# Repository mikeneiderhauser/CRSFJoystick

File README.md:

# ELRSJoystick / CRSFJoystick

<https://github.com/mikeneiderhauser/CRSFJoystick>

Named CRSFJoystick as it indicates the wire protocol between the microcontroller (pi pico) and receiver).

Arduino code using the mbed core that runs on a Pi Pico (2040) to emulate a USB HID Joystick

Pirmarily developed to use and ExpressLRS receiver and a HID Joystick for Sim use! It will work with both Tracer and Crossfire as well.

Shout out to CapnBry for the Crsf Library

https://github.com/CapnBry/CRServoF

Shout out to RealRobots.net for the Gamepad Library

https://gitlab.com/realrobots/PicoGamepad/-/tree/master

# Future Plans

- GitHub Builds
- Rework HID USB code
- Add failsafe nopulses / hold

# Demo Video

## Purchase

Originally offered of FPVExchange, but that is no longer an option. Please send me an email for availability, purchase, or to get additional info!

<housefpv@gmail.com>

You can also contact me on discord [HouseFPV](https://discordapp.com/users/HouseFPV#5899)

- Blank carrier boards for Pi Pico, Tiny 2040, and Waveshare RP2040 (old stock)
- Built and flashed units
- [DIY Section](#diy-hardware)

A few boards that I believe are based off of this project:
- HGLRC Dongle (I have samples from HGLRC on the way)
  - [HGLRC Dongle at HGLRC](https://www.hglrc.com/collections/new-arrivals/products/hglrc-c1-remote-control)
  - [HGLRC C1 Radio Kit with dongle at HGLRC](https://www.hglrc.com/collections/new-arrivals/products/hglrc-c1-remote-control)
  - [HGLRC C1 Radio Kit with dongle at RacedayQuads](https://www.racedayquads.com/products/hglrc-c1-transmitter-elrs-2-4ghz-choose-your-version?keyword=hglrc%20c1)
- Squid Stick (I have personally not tested one)
  -  [Squid Stick at Progressiverc.com](https://www.progressiverc.com/products/squid-stick-elrs-2-4ghz-usb-receiver-module)
  -  Squid Stick at RacedayQuads - Link to be posted when available
- YMZFPV Simulator Adapter (have not yet been able to confirm that this is based off of this project)
  - [YMZFPV Sim Adapter at RacedayQuads](https://www.racedayquads.com/products/ymzfpv-wireless-simulator-adapter-for-sbus-pwm-csfr-choose-your-version?keyword=simulator)

## Compatability

This project was designed primarily with ELRS usage in mind, however this code base has also been tested with TBS Crossfire Receivers (915MHZ) (last tested v6.16) and TBS Tracer Receivers (2.4GHz) (last tested v6.17) and both appear to work! Flight was teseted in the Liftoff simulator.

I no longer have TBS Crossfire nor TBS Tracer TX modules or Receivers so future tests will have to be conducted by others.

### ExpressLRS (Waveshare RP2040)

### Crossfire

### Tracer

# Building / Flashing

I recently converted the projet to PlatformIO to aid in building, board management, etc.  PlatformIO has some known quirks with PiPico boards and I'm going to leave some breadcrumbs here for later.

## VSCode with PlatformIO

### Installing VSCode and PlatformIO
<https://platformio.org/install/ide?install=vscode>

### Build for specific board / environment

At the Bottom of VSCode you will see a tool bar.  Look for `Default (CRSFJoystick)`.  Building in this state will build for all boards / environments defined in the `platformio.ini` file.  To target a sepecific board, Click on `Default (CRSFJoystick)` and select an appropriate option (Note, selection pops up at the top of vscode).

Click on the Checkmark on the bottom toolbar to build for the board / environment you selected.

Click on the `->` on the bottom toolbar to upload to the board.  If upload fails to find your board, please see bothe the [alternative upload](#alternative-upload) section as well as the driver section.

## Alternative upload
This is one of the standard advertised methods for uploading firmware to a pipico based microcontroller board.

Press and hold the bootsel button on your board and either plugin/power on the board or if the board is already powered press and release the reset button.

This will put the board in RP2 Boot mode.

A removable device should pop up or become available on your computer.  Drag and drop the `firmware.u2f` file from the `.pio/build/wavesharerp2040zero/` directory into this device on your computer.  Note replpace wavesharerp2040zero with the environment for your board.

## Drivers
Drivers can be hit or miss for the pipico board and platformio.  

You may need to use zadig to get vscode+platforio to be able to upload directly to the board.
<https://github.com/platformio/platform-raspberrypi/issues/2#issuecomment-828586398>

Below are the drivers I have working on my Windows 11 machine.  You may need to modify the driver selection via zadig and or device manager to get it working.

- Standard Running Mode
  - RaspberryPi Pico (Interface 0)
    - Zadig -> HidUsb v10.0.22621.819
    - Device Manager -> Human Interface Devices -> HID-compliant game controller
  - RaspberryPi Pico (Interface 1)
      - Zadig -> usbser v10.0.22621.1778
      - Device Manager -> Ports (COM & LPT) -> USB Serial Device
- RP2 Boot mode
  - RP2 Boot (Interface 0) 
    - Zadig USBSTOR v10.0.022621.1778 
    - Device Manager -> Disk Drives -> RPI RP2 USB Device 
  - RP2 Boot (Interface 1)
    - Zadig WinUSB v6.1.7600.16385
    Device Manager -> Universal Serial Bus Devices -> RP2 Boot

### Device manager clicks to change driver 
Right Click -> Properties -> Update Driver -> Browse my computer for drivers -> Let me pick from a list of available drivers on my computer

# Flashing ELRS Receiver

Depending on the device you are using, your target may be different.  For all of the DIY version's I've made, I used the HappyModel EP2 Rx.  Other vendors may vary.

## Flashing via Betaflight Passthrough
<https://www.expresslrs.org/software/updating/betaflight-passthrough/>

## Flashing via Wifi
If your receiver is wifi enabled you can also flash it via wifi

<https://www.expresslrs.org/software/updating/wifi-updating/>

# Testing
For a quick test of functionality, I typically go to [GamepadTester](https://hardwaretester.com/gamepad).

Once the Radio is bound to the RX, it should show up in GamePadTester.

# Mappings
This was a quick map and is not fully featured.

On link up/down the onboard Pi Pico LED will light indicating connection

*NOTE* Channel 5, 6, 7, and 8 are mapped both to analog axis as well as joystick buttons.

| Channel     | Logical Mapping  | Joystick Mapping |
| ----------- | ---------------- | ---------------- |
| 1           | A                | X                |
| 2           | E                | Y                |
| 3           | T                | Rx               |
| 4           | R                | Ry               |
| 5           | Channel 5 (Full) AND AUX1 (1510-2011) | Z  AND Button 0 |
| 6           | Channel 6 (Full) AND AUX2 (1510-2011) | Rz AND Button 1 |
| 7           | Channel 7 (Full) AND AUX3 (1510-2011) | S0 AND Button 2 |
| 8           | Channel 8 (Full) AND AUX4 (1510-2001) | S1 AND Button 3 |
| 9           | AUX5 (1510-2011) | Button 4         |
| 10          | AUX6 (1510-2011) | Button 5         |
| 11          | AUX7 (1510-2011) | Button 6         |
| 12          | AUX8 (1510-2011) | Button 7         |
| 13          | Not Used         | Not Used         |
| 14          | Not Used         | Not Used         |
| 15          | LQ - Not Used    | Not Used         |
| 16          | RSSI - Not Used  | Not Used         |

*Note additional button mappings can be created in caliration.h*

# Here below is for DIY Builds and may be slightly outdated
# DIY Hardware

In a nutshell, wire the ELRS RX up to a uart on the pipico, 5v, and gnd.

| Raspberry Pico | ELRS/CRSF Receiver |
| -------------- | ------------------ |
| VBUS (PIN 40)  | 5V                 |
| GND  (PIN 38)  | GND
| GP4  (PIN 6)   | RX                 |
| GP5  (PIN 7)   | TX                 |

Other boards are supported, see the [board_defs.h](./include/board_defs.h) file.

| Part  | Link | Approx Cost |
| ----- | ---- | ------------|
| Pi Pico | https://www.pishop.us/product/raspberry-pi-pico/ | $4 (Approx $6 with shipping) |
| Waveshare RP2040 zero | https://www.amazon.com/RP2040-Zero-Development-Microcontroller-Multi-Function-Integration/dp/B09SBCKYSC/ref=sr_1_1_sspa?crid=1NDXW0KFV39DX&keywords=waveshare+rp2040+zero&qid=1697989796&sprefix=waveshare+rp2040+zero%2Caps%2C66&sr=8-1-spons&sp_csd=d2lkZ2V0TmFtZT1zcF9hdGY&psc=1| $10|
| Tiny 2040 (alt part) | https://www.pishop.us/product/tiny-2040/ | $10 (Approx $12 with shipping) |
| ELRS RX (any will do) |  https://www.racedayquads.com/products/happymodel-2-4ghz-ep2-tcxo-rx-express-lrs-receiver?keyword=expresslrs | $18 |

Note, price breaks can be had when purchasing at quantity.

Approx part cost for pico hardware (large footprint, cheaper) - $20-$25

- Pi Pico - $4.00
- ELRS RX - $13.50 
- Carrier Board - $1.00 (approx)
- Shipping / Tax from vendors - varies

# Carrier Boards

## ELRSJoystick

This board has an ELRS RX built in, so you don't need to wire any RX on, just plug in and connect to your ELRS TX, then you are ready to go!

## Tiny Version

> **_NOTE:_** References to level shifters below are no longer needed as the level shifter can be omitted. You will have to bridge the pads on the level shifter for the TX/RX pins or use a newer version of the carrier board.

I personally use the Waveshare RP2040-Zero version for my ELRS Joystick!

Hardware build files are located in hardware/kicad/CRSFJoystick/output/Rev1.0

I used JLCPCB with Black Soldermask and a board thickness of 1.6mm.

Note the different orientation of the ELRS RX's.  The orientation can be flipped.  I installed each RX to ensure the boot pad is exposed should the RX need recovered.

## Waveshare RP2040-Zero

[WaveShare RP2040-Zero Board](https://www.waveshare.com/rp2040-zero.htm)

## Raspberry Pi Pico (Full Version)

## Tiny2040

## SEEED AXIO 2040

Board files now in the hardware folder.  Not built or tested but should work.

[SEEED XAIO RP2040 Board](https://www.seeedstudio.com/XIAO-RP2040-v1-0-p-5026.html)

## CRSFJoystick2.0

Build a smaller pico by yourself.

# General Assembly

- Print the top and bottom enclosure
- Print 2 of the spacers for the Pi2040, Print 4 of the spacers for the Pi Pico version
- Follow the directions in this video https://youtu.be/Zuhfbobgm5A

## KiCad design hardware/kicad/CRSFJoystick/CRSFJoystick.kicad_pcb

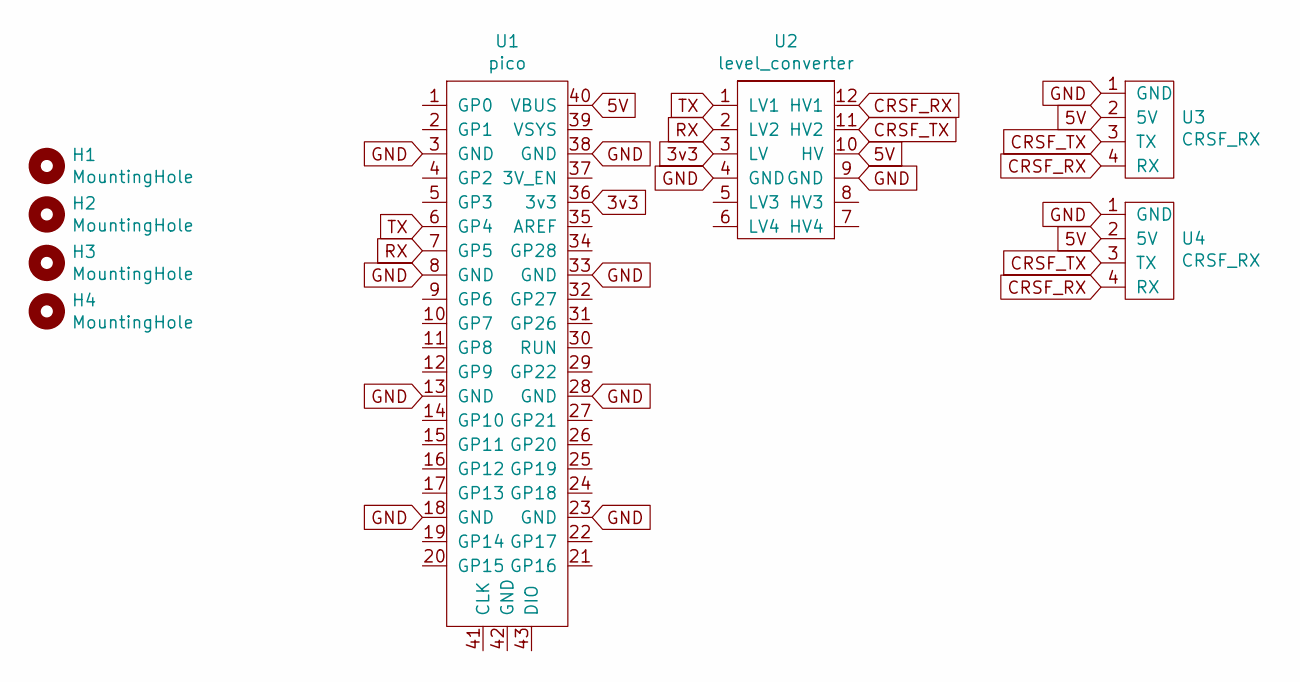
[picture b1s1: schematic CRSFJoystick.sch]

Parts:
H1, H2, H3, H4: MountingHole; MountingHole_2.2mm_M2
U1: pico; pico_no_swd
U2: level_converter
U3, U4: CRSF_RX; ELRS_EP2

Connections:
3v3: U1.36 (3v3), U2.3 (LV)
5V: U1.40 (VBUS), U2.10 (HV), U3.2 (5V), U4.2 (5V)
CRSF_RX: U2.12 (HV1), U3.4 (RX), U4.4 (RX)
CRSF_TX: U2.11 (HV2), U3.3 (TX), U4.3 (TX)
GND: U1.3 (GND), U1.8 (GND), U1.13 (GND), U1.18 (GND), U1.23 (GND), U1.28 (GND), U1.33 (GND), U1.38 (GND), U2.4 (GND), U2.9 (GND), U3.1 (GND), U4.1 (GND)
RX: U1.7 (GP5), U2.2 (LV2)
TX: U1.6 (GP4), U2.1 (LV1)

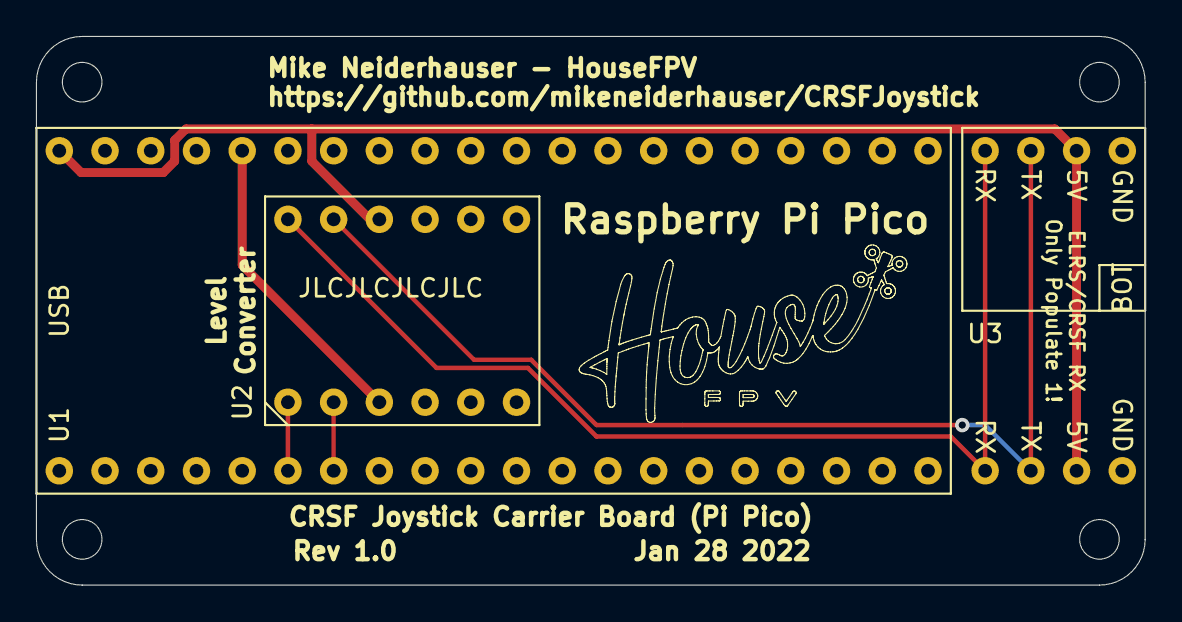
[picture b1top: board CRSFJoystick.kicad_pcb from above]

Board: 2 copper layers, 61.6 x 30.5 mm, 8 parts (1 on the bottom side), 7 nets.

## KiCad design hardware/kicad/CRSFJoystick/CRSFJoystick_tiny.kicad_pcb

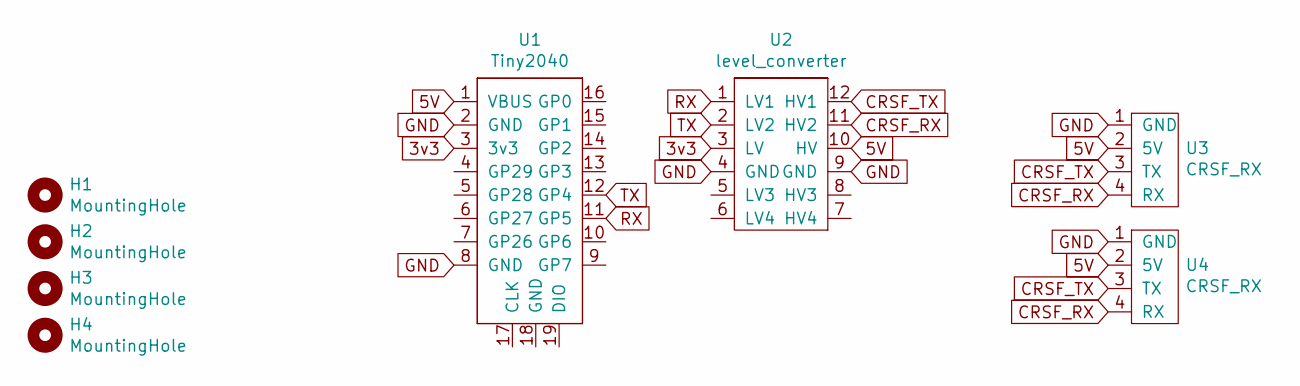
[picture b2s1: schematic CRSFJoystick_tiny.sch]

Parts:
H1, H2, H3, H4: MountingHole; MountingHole_2.2mm_M2
U1: Tiny2040; tiny2040_no_swd
U2: level_converter
U3, U4: CRSF_RX; ELRS_EP2

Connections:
3v3: U1.3 (3v3), U2.3 (LV)
5V: U1.1 (VBUS), U2.10 (HV), U3.2 (5V), U4.2 (5V)
CRSF_RX: U2.11 (HV2), U3.4 (RX), U4.4 (RX)
CRSF_TX: U2.12 (HV1), U3.3 (TX), U4.3 (TX)
GND: U1.2 (GND), U1.8 (GND), U2.4 (GND), U2.9 (GND), U3.1 (GND), U4.1 (GND)
RX: U1.11 (GP5), U2.1 (LV1)
TX: U1.12 (GP4), U2.2 (LV2)

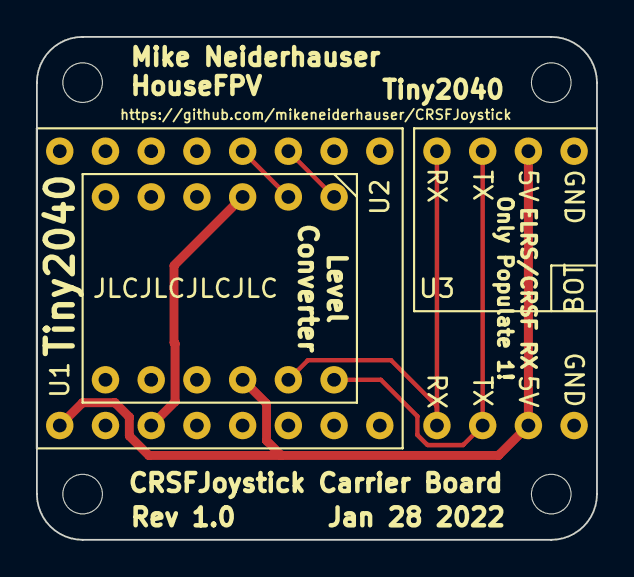
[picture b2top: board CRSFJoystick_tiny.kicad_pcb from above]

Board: 2 copper layers, 31.1 x 27.9 mm, 8 parts (1 on the bottom side), 7 nets.

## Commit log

2022-01-20 Initial checkin
2022-01-20 Add some usage instructions and future plans
2022-01-21 Add ability to map aux ranges to buttons. Multi position support
2022-01-21 Add Demo vid. Configurable buttons
2022-01-29 Add kicad project files and gerber files
2022-01-29 Add proto carrier boards to README
2022-02-25 Add Build Photos
2022-03-03 Update Channel mapping to support first 4 aux channels as full resolution
2022-03-14 add stl files for enclosures
2022-03-14 changes to readme adding prints and level shifter pictures
2022-03-19 Port to Seeed XIAO RP2040
    Added port to Seeed XIAO RP2040 that uses Adafruit TinyUSB.
    Need to install the Seeed XIAO RP2040 board and slect the Adafruit TinyUSB stack to build.
2022-04-02 Add UART define for SEEED XIAO board
2022-04-12 Add LED Libs
2022-04-12 Code changes for board specific LED changes
2022-04-12 Add firmware elf and uf2 for 1.0.1
2022-05-02 Add gerber files for R1.1 that removes level converter
2022-05-02 Added Waveshare RP2040-Zero files
2022-05-08 Add XIAO RP2040 board
2022-05-23 changes to readme adding prints and pictures for Waveshare 2040
2022-06-04 Defaulting to Waveshare board. Removing typo in setup
2022-11-11 Support for Pro Micro.
2022-11-29 New 2.0 version 1. A new usb version hardware. 2. Update all libraries to the latest version.
2022-11-29 added case for CRSFJoystick2.0
2022-11-29 add case for CRSFJoystick2.0
2022-11-29 move gerber file to a new folder
2022-11-29 2.0 version 1. A new usb version hardware. 2. Update all libraries to the latest version.
2022-11-29 add bom file
2022-11-30 fixed a bom error
2022-12-28 v2.2 version
2022-12-28 slightly change
2023-02-02 v2.4
2023-02-02 v2.3
2023-02-10 small modifications
2023-03-13 1.button mapping is now the same as EdgeTX default 2.led blinks when connection is down(same as ELRS)
2023-03-13 changed readme
2023-03-21 LED blinks for 60 sec when connection is down.
2023-03-22 Implement 60 sec non-blocking blink routine
2023-03-22 Restore button count to 8
2023-05-11 fix serial passthru
2023-05-11 tidy up
2023-05-21 comment out PiPico - Make Waveshare default build
2023-09-28 Minor update to readme.
2023-10-18 Add schematic file
2023-10-22 Rework repository to work with PlatformIO
2023-10-23 add schematic of CRSFJoystick2.0 and ELRSJoystick
2023-10-23 rename folder
2023-10-23 reorder folders
2023-10-24 fix folder name error
2023-10-24 Add files via upload
    Add receiver schematic
2023-11-25 Add pin reference table for Pi Pico
2023-12-03 make the hole bigger to meet JLC's free policy
2024-02-03 Add support for Adafruit QT Py RP2040 board.
2025-05-16 Betaflight's CLI only requires hash, not CRLF so recent ELRS upload doesn't work
2025-08-01 Move from Adafruit Neopixel libs to Neopixel Connect libs
